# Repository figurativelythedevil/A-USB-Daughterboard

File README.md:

A work in progress.

This is a USB-C daughterboard with a 4-port USB 2.0 hub on it (2 USB-A, 2 internal facing connectors on JST SR connectors), based around the Microchip USB2514 IC.

Many thanks to:
* The [C3 Unified Daughterboard](https://github.com/ai03-2725/Unified-Daughterboard) project, form which this daughterboard was based off of 
* The [Nanohub Project](https://hackaday.io/project/20790-nanohub-tiny-usb-20-and-30-hubs) - the USB2514 schematic was partially referenced off of the 4-port USB 2.0 design

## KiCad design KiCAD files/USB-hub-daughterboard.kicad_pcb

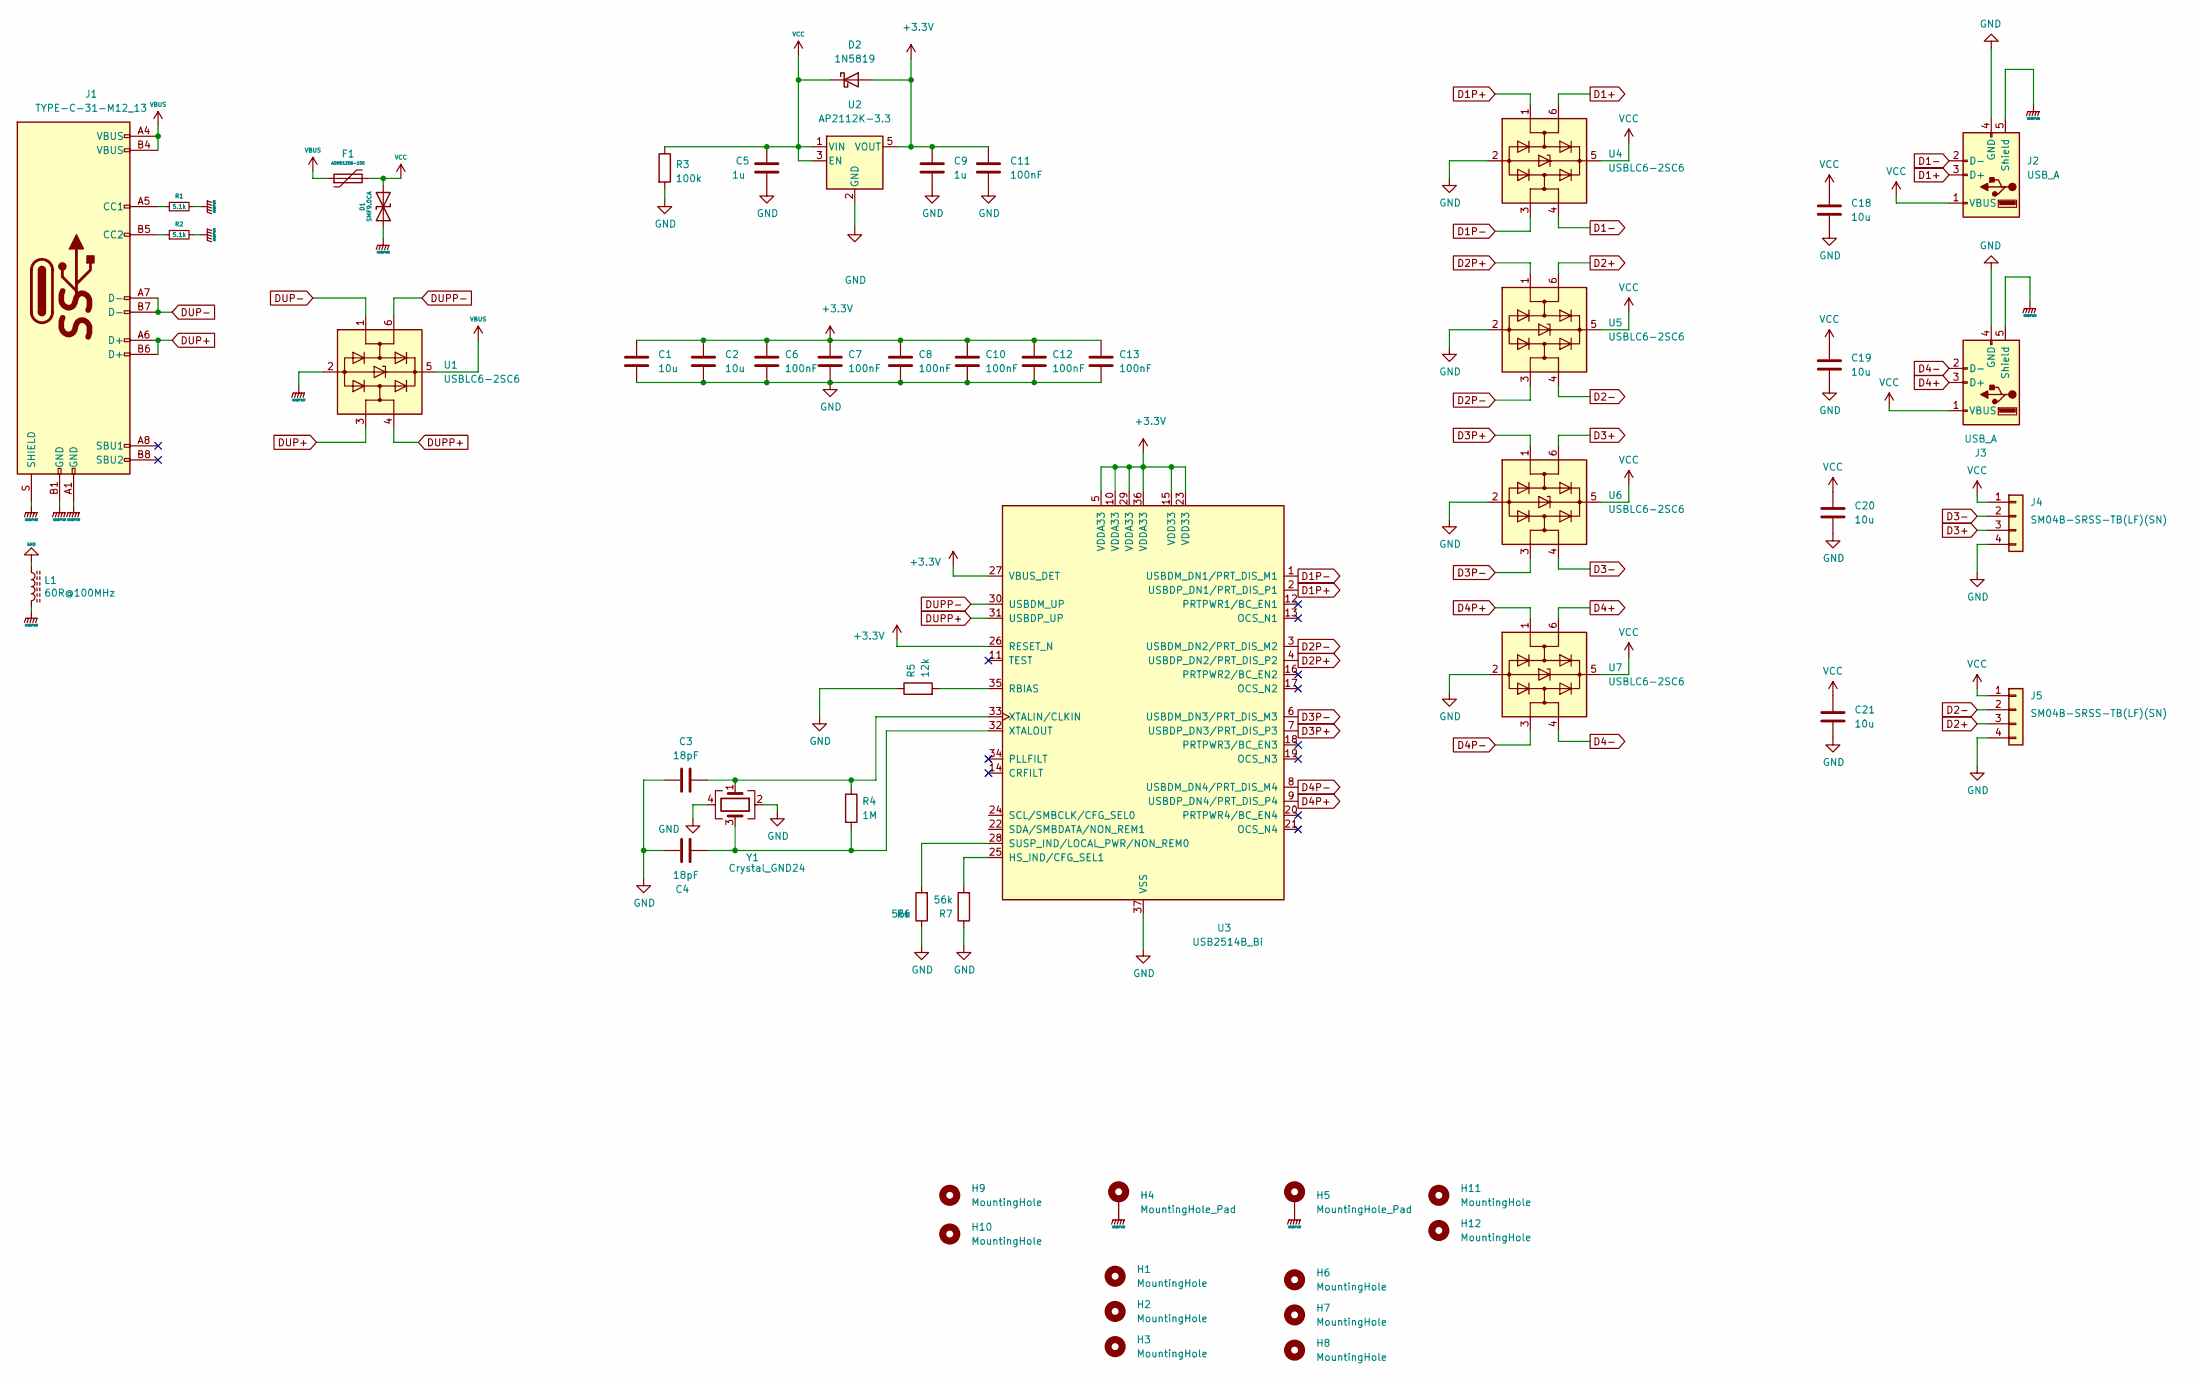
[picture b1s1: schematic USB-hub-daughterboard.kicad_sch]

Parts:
C1, C2, C18, C19, C20, C21: 10u; C_0805_2012Metric_Pad1.15x1.40mm_HandSolder
C3, C4: 18pF; C_0603_1608Metric_Pad1.05x0.95mm_HandSolder
C5, C9: 1u; C_0805_2012Metric_Pad1.15x1.40mm_HandSolder
C6, C7, C8, C10, C11, C12, C13: 100nF; C_0603_1608Metric_Pad1.05x0.95mm_HandSolder
D1: SMF9.0CA; D_SOD-123_Bidirectional; Manufacturer Part No SMF9.0CA; LCSC Part No C123799
D2: 1N5819; D_SOD-123
F1: ASMD1206-150; Fuse_1206_3216Metric; Manufacturer Part No ASMD1206-150; LCSC Part No C135342
H1, H2, H3, H9, H10: MountingHole; MountingHole_3.2mm_M3_ISO7380
H4: MountingHole_Pad; MountingHole_3.2mm_M3_ISO7380_Pad
H5: MountingHole_Pad; MountingHole_2.2mm_M2_ISO7380_Pad
H6, H7, H8, H11, H12: MountingHole; MountingHole_2.2mm_M2_ISO7380
J1: TYPE-C-31-M12_13; TYPE-C-31-M-12
J2, J3: USB_A; USB_A_Molex_67643_Horizontal
J4, J5: SM04B-SRSS-TB(LF)(SN); Manufacturer Part No SM04B-SRSS-TB(LF)(SN); LCSC Part No C160404
L1: 60R@100MHz; L_1206_3216Metric; Manufacturer Part No MLB3216-600P4A(f); LCSC Part No C33600
R1, R2: 5.1k; R_0805_2012Metric_Pad1.15x1.40mm_HandSolder
R3: 100k; R_0805_2012Metric_Pad1.15x1.40mm_HandSolder
R4: 1M; R_0805_2012Metric_Pad1.15x1.40mm_HandSolder
R5: 12k; R_0805_2012Metric_Pad1.15x1.40mm_HandSolder
R6, R7: 56k; R_0805_2012Metric_Pad1.15x1.40mm_HandSolder
U1, U4, U5, U6, U7: USBLC6-2SC6; SOT-23-6
U2: AP2112K-3.3; SOT-23-5
U3: USB2514B_Bi; QFN-36-1EP_6x6mm_P0.5mm_EP3.7x3.7mm
Y1: Crystal_GND24; Crystal_SMD_3225-4Pin_3.2x2.5mm_HandSoldering

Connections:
+3V3: C1.1, C2.1, C6.1, C7.1, C8.1, C9.1, C10.1, C11.1, C12.1, C13.1, D2.2 (A), U2.5 (VOUT), U3.5 (VDDA33), U3.10 (VDDA33), U3.15 (VDD33), U3.23 (VDD33), U3.26 (RESET_N), U3.27 (VBUS_DET), U3.29 (VDDA33), U3.36 (VDDA33)
D1+: J2.3 (D+), U4.6 (I/O1)
D1-: J2.2 (D-), U4.4 (I/O2)
D1P+: U3.2 (USBDP_DN1/PRT_DIS_P1), U4.1 (I/O1)
D1P-: U3.1 (USBDM_DN1/PRT_DIS_M1), U4.3 (I/O2)
D2+: J5.3, U5.6 (I/O1)
D2-: J5.2, U5.4 (I/O2)
D2P+: U3.4 (USBDP_DN2/PRT_DIS_P2), U5.1 (I/O1)
D2P-: U3.3 (USBDM_DN2/PRT_DIS_M2), U5.3 (I/O2)
D3+: J4.3, U6.6 (I/O1)
D3-: J4.2, U6.4 (I/O2)
D3P+: U3.7 (USBDP_DN3/PRT_DIS_P3), U6.1 (I/O1)
D3P-: U3.6 (USBDM_DN3/PRT_DIS_M3), U6.3 (I/O2)
D4+: J3.3 (D+), U7.6 (I/O1)
D4-: J3.2 (D-), U7.4 (I/O2)
D4P+: U3.9 (USBDP_DN4/PRT_DIS_P4), U7.1 (I/O1)
D4P-: U3.8 (USBDM_DN4/PRT_DIS_M4), U7.3 (I/O2)
DUP+: J1.A6 (D+), J1.B6 (D+), U1.3 (I/O2)
DUP-: J1.A7 (D-), J1.B7 (D-), U1.1 (I/O1)
DUPP+: U1.4 (I/O2), U3.31 (USBDP_UP)
DUPP-: U1.6 (I/O1), U3.30 (USBDM_UP)
GND: C1.2, C2.2, C3.1, C4.1, C5.2, C6.2, C7.2, C8.2, C9.2, C10.2, C11.2, C12.2, C13.2, C18.2, C19.2, C20.2, C21.2, J2.4 (GND), J3.4 (GND), J4.4, J5.4, L1.1, R3.2, R5.1, R6.1, R7.1, U2.2 (GND), U3.37 (VSS), U4.2 (GND), U5.2 (GND), U6.2 (GND), U7.2 (GND), Y1.2, Y1.4
GNDPWR: D1.1 (A1), H4.1, H5.1, J1.A1 (GND), J1.B1 (GND), J1.S (SHIELD), J2.5 (Shield), J3.5 (Shield), L1.2, R1.2, R2.2, U1.2 (GND)
unnamed: C3.2, R4.1, U3.33 (XTALIN/CLKIN), Y1.1
unnamed: C4.2, R4.2, U3.32 (XTALOUT), Y1.3
unnamed: J1.A5 (CC1), R1.1
unnamed: J1.B5 (CC2), R2.1
unnamed: R5.2, U3.35 (RBIAS)
unnamed: R6.2, U3.28 (SUSP_IND/LOCAL_PWR/NON_REM0)
unnamed: R7.2, U3.25 (HS_IND/CFG_SEL1)
VBUS: F1.1, J1.A4 (VBUS), J1.B4 (VBUS), U1.5 (VBUS)
VCC: C5.1, C18.1, C19.1, C20.1, C21.1, D1.2 (A2), D2.1 (K), F1.2, J2.1 (VBUS), J3.1 (VBUS), J4.1, J5.1, R3.1, U2.1 (VIN), U2.3 (EN), U4.5 (VBUS), U5.5 (VBUS), U6.5 (VBUS), U7.5 (VBUS)

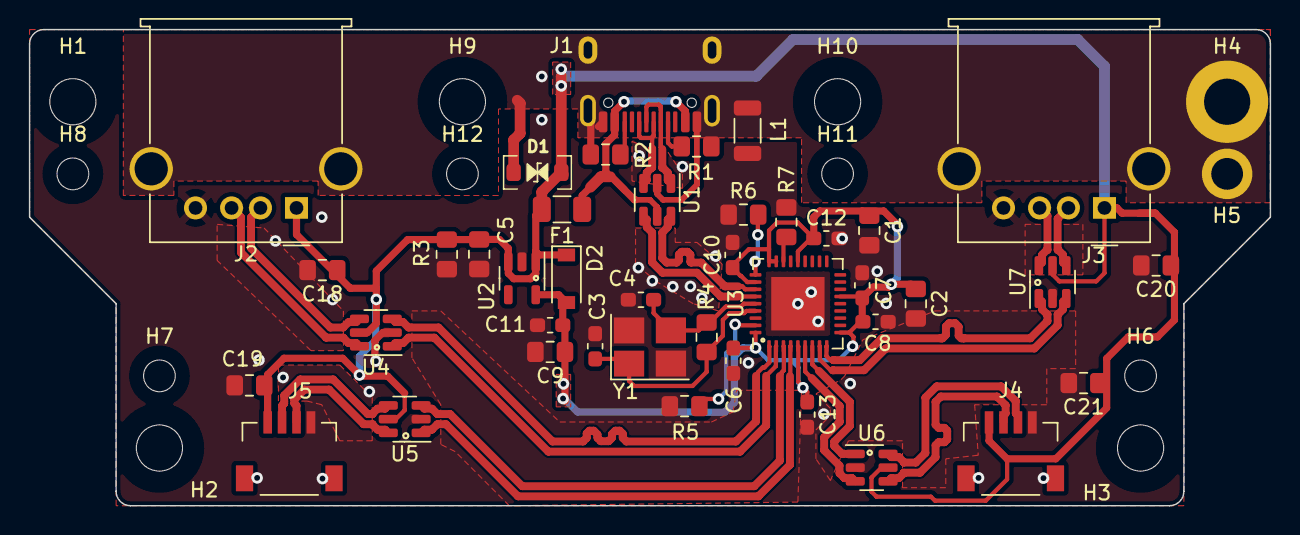
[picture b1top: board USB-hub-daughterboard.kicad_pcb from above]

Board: 2 copper layers, 86.0 x 33.0 mm, 53 parts (0 on the bottom side), 32 nets.

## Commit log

2021-02-25 Work in progress updates
2021-02-28 More layout work
2021-02-28 Initial revision
2021-02-28 More work
2021-02-28 Added picture
2021-02-28 Slightly improved routing, made PCB 1.2mm thick
2021-04-11 Forked from Pylon for reference
2021-04-12 Tweaks
